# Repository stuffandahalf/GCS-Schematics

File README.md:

# GCS-Schematics
Schematics for my 8-bit computer

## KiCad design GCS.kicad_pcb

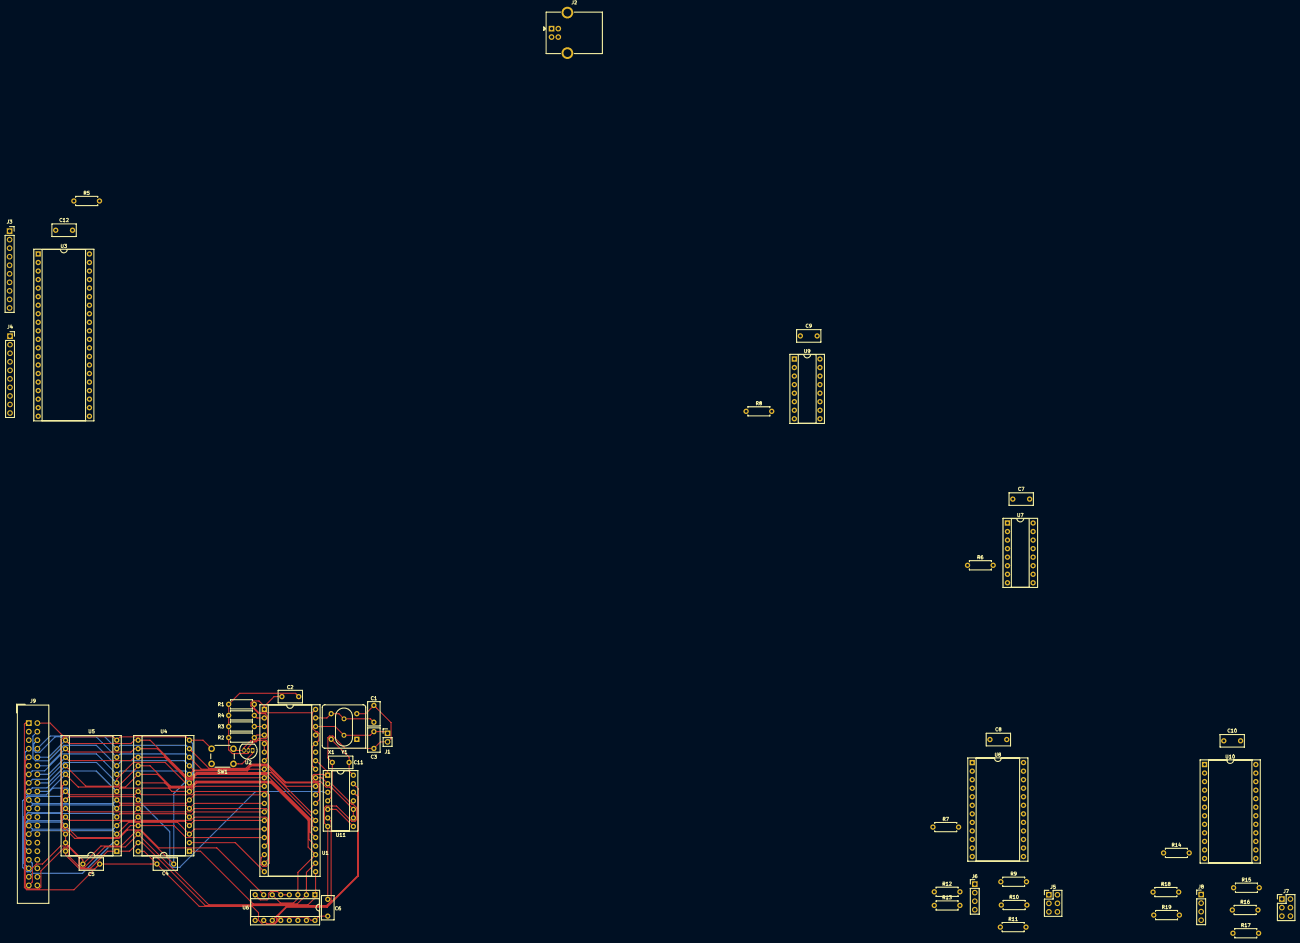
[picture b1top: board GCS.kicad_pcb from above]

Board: 2 copper layers, 54 parts (0 on the bottom side), 91 nets.

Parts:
C1, C3: 15nF; C_Rect_L7.0mm_W3.5mm_P5.00mm
C2, C4, C5, C6, C7, C8, C9, C10, C11, C12: 100nF; C_Rect_L7.0mm_W3.5mm_P5.00mm
J1: PROC_EXTAL_GND; PinHeader_1x02_P2.54mm_Vertical
J2: USB_B; USB_B_OST_USB-B1HSxx_Horizontal
J3: PA_CON; PinSocket_1x10_P2.54mm_Vertical
J4: PB_CON; PinSocket_1x10_P2.54mm_Vertical
J5: ASYNC0_OPT; PinHeader_2x03_P2.54mm_Vertical
J6: ASYNC0_IO; PinHeader_1x04_P2.54mm_Vertical
J7: ASYNC1_OPT; PinHeader_2x03_P2.54mm_Vertical
J8: ASYNC1_IO; PinHeader_1x04_P2.54mm_Vertical
J9: Conn_02x20_Odd_Even; IDC-Header_2x20_P2.54mm_Vertical
R1, R2, R3, R4, R5, R6, R7, R8, R9, R10, R11, R12, R13, R14, R15, R16, R17, R18, R19: 2.7k; R_Axial_DIN0207_L6.3mm_D2.5mm_P7.62mm_Horizontal
SW1: SW_Push; SW_PUSH_6mm
U1: MC6809; DIP-40_W15.24mm_Socket
U2: DS1813; TO-92_Inline
U3: MC68B21; DIP-40_W15.24mm_Socket
U4: HM62256BLP-7; DIP-28_W15.24mm_Socket
U5: 29C256; DIP-28_W15.24mm_Socket
U6, U7, U9: 74LS138; DIP-16_W7.62mm_Socket
U8, U10: MC6850; DIP-24_W15.24mm_Socket
U11: 74HCT00; DIP-14_W7.62mm_Socket
X1: CXO_DIP8; Oscillator_DIP-8
Y1: Crystal; Crystal_HC18-U_Vertical

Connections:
/A0: J9.13, U1.8, U3.36, U4.10, U5.10, U8.11, U10.11
/A1: J9.15, U1.9, U3.35, U4.9, U5.9
/A2: J9.17, U1.10, U4.8, U5.8
/A3: J9.19, U1.11, U4.7, U5.7
/A4: J9.21, U1.12, U4.6, U5.6, U9.1
/A5: J9.23, U1.13, U4.5, U5.5, U9.2
/A6: J9.25, U1.14, U4.4, U5.4, U9.3
/A7: J9.27, U1.15, U4.3, U5.3
/A8: J9.29, U1.16, U4.25, U5.25
/A9: J9.31, U1.17, U4.24, U5.24
/A10: J9.33, U1.18, U4.21, U5.21, U7.1
/A11: J9.35, U1.19, U4.23, U5.23, U7.2
/A12: J9.37, U1.20, U4.2, U5.2, U7.3
/A13: J9.39, U1.21, U4.26, U6.1
/A14: U1.22, U4.1, U6.2
/A15: U1.23, U4.20, U6.3, U6.6
/D0: J9.4, U1.31, U3.33, U4.11, U5.11
/D1: J9.6, U1.30, U3.32, U4.12, U5.12
/D2: J9.8, U1.29, U3.31, U4.13, U5.13
/D3: J9.10, U1.28, U3.30, U4.15, U5.15
/D4: J9.12, U1.27, U3.29, U4.16, U5.16
/D5: J9.14, U1.26, U3.28, U4.17, U5.17
/D6: J9.16, U1.25, U3.27, U4.18, U5.18
/D7: J9.18, U1.24, U3.26, U4.19, U5.19
/E: J9.3, U1.34, U3.25, U8.3, U8.4, U8.14, U10.3, U10.4, U10.14, U11.1, U11.4
/EXTAL: C3.1, J1.1, U1.38, Y1.2
/RX0: R12.2, U8.2
/RX1: R18.2, U10.2
/R~W: J9.5, U1.32, U3.21, U8.13, U10.13, U11.2, U11.9, U11.10
/TX0: R13.2, U8.6
/TX1: R19.2, U10.6
/XTAL: C1.1, U1.39, X1.5, Y1.1
/~ASYNC0_E: U8.9, U9.13
/~ASYNC1_E: U9.12, U10.9
/~BRAM0: U6.11, U11.12
/~BRAM1: U6.10, U11.13
/~CTS0: R10.2, U8.24
/~CTS1: R16.2, U10.24
/~DCD0: R9.2, U8.23
/~DCD1: R15.2, U10.23
/~FIRQ: R2.2, U1.4
/~INT_IO: U7.15, U9.5
/~IO: U6.9, U7.5
/~IRQ: R3.2, U1.3, U3.37, U3.38, U8.7, U10.7
/~NMI: R4.2, U1.2
/~PIA_E: U3.23, U9.14
/~R: J9.7, U4.22, U5.22, U11.3
/~RESET: SW1.2, U1.37, U2.1, U3.34
/~ROM: U5.20, U6.7
/~RTS0: R11.2, U8.5
/~RTS1: R17.2, U10.5
/~R~W: U11.5, U11.8
/~W: J9.9, U4.27, U5.1, U11.6
GND: C1.2, C2.2, C3.2, C4.2, C5.2, C6.2, C7.2, C8.2, C9.2, C10.2, C11.2, C12.2, J1.2, J2.4, J5.2, J5.4, J5.6, J6.1, J7.2, J7.4, J7.6, J8.1, J9.2, SW1.1, U1.1, U2.3, U3.1, U4.14, U5.14, U5.26, U5.27, U6.4, U6.5, U6.8, U7.4, U7.8, U8.1, U9.4, U9.8, U10.1, U11.7, X1.4
unnamed: J3.1, U3.2
unnamed: J3.2, U3.3
unnamed: J3.3, U3.4
unnamed: J3.4, U3.5
unnamed: J3.5, U3.6
unnamed: J3.6, U3.7
unnamed: J3.7, U3.8
unnamed: J3.8, U3.9
unnamed: J3.9, U3.40
unnamed: J3.10, U3.39
unnamed: J4.1, U3.10
unnamed: J4.2, U3.11
unnamed: J4.3, U3.12
unnamed: J4.4, U3.13
unnamed: J4.5, U3.14
unnamed: J4.6, U3.15
unnamed: J4.7, U3.16
unnamed: J4.8, U3.17
unnamed: J4.9, U3.18
unnamed: J4.10, U3.19
unnamed: J5.1, R9.1
unnamed: J5.3, R10.1
unnamed: J5.5, R11.1
unnamed: J6.2, R13.1
unnamed: J6.3, R12.1
unnamed: J7.1, R15.1
unnamed: J7.3, R16.1
unnamed: J7.5, R17.1
unnamed: J8.2, R19.1
unnamed: J8.3, R18.1
unnamed: R1.2, U1.33, U1.36, U1.40
unnamed: R5.1, U3.22, U3.24
unnamed: R6.1, U7.6
unnamed: R7.1, U8.8, U8.10
unnamed: R8.1, U9.6
unnamed: R14.1, U10.8, U10.10
VCC: C2.1, C4.1, C5.1, C6.1, C7.1, C8.1, C9.1, C10.1, C11.1, C12.1, J2.1, J6.4, J8.4, J9.1, R1.1, R2.1, R3.1, R4.1, R5.2, R6.2, R7.2, R8.2, R14.2, U1.7, U2.2, U3.20, U4.28, U5.28, U6.16, U7.16, U8.12, U9.16, U10.12, U11.14, X1.8

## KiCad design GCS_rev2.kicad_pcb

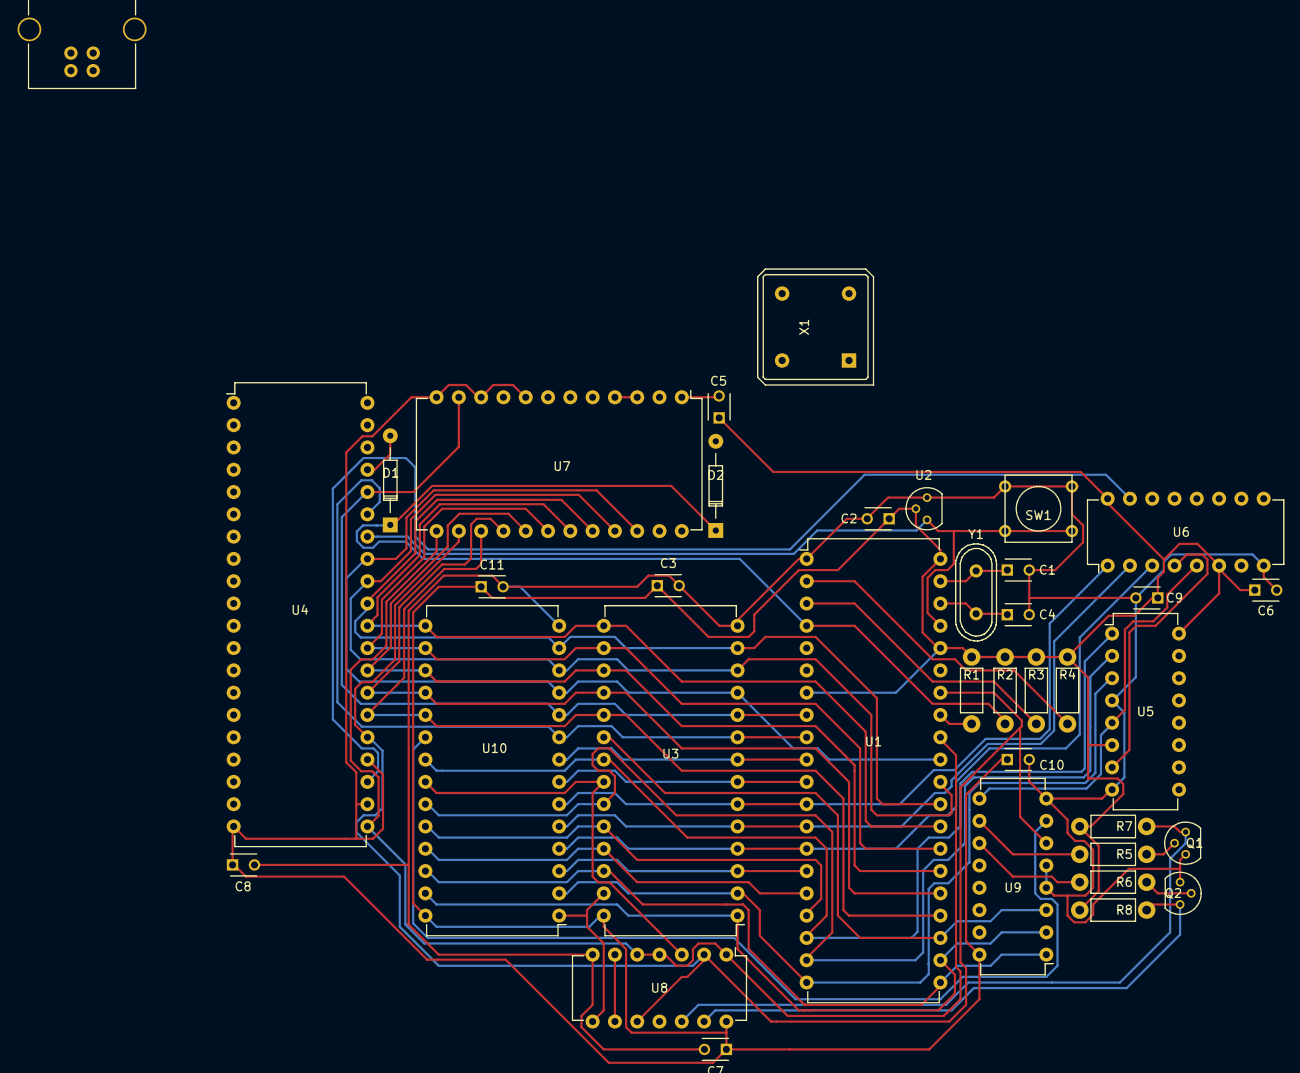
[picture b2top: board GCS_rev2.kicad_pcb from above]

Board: 2 copper layers, 37 parts (0 on the bottom side), 52 nets.

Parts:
C1, C4: 15p; C_Disc_D3_P2.5
C2, C3, C5, C6, C7, C8, C9, C10, C11: .1u; C_Disc_D3_P2.5
D1, D2: D; Diode_DO-35_SOD27_Horizontal_RM10
P1: USB_B
Q1, Q2: 2N3904; TO-92_Molded_Narrow
R1, R2, R3, R4: 4.7k; Resistor_Horizontal_RM7mm
R5, R6: 1k; Resistor_Horizontal_RM7mm
R7, R8: 220; Resistor_Horizontal_RM7mm
SW1: SW_PUSH; SW_PUSH_SMALL
U1: MC6809; DIP-40_W15.24mm
U2: DS1813-5; TO-92_Molded_Narrow
U3: HM62256BLP-7; DIP-28_W15.24mm
U4: 6821; DIP-40_W15.24mm
U5, U6, U9: 74LS138; DIP-16_W7.62mm
U7: MC6850; DIP-24_W15.24mm
U8: 74LS00; DIP-14_W7.62mm
U10: AT29C256-90PI; DIP-28_W15.24mm
X1: CXO_DIP8; OSC_DIP8
Y1: Crystal; Crystal_HC49-U_Vertical

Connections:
/A0: U1.8, U3.10, U4.36, U7.11, U10.10
/A1: U1.9, U3.9, U4.35, U10.9
/A2: U1.10, U3.8, U10.8
/A3: U1.11, U3.7, U10.7
/A4: U1.12, U3.6, U6.1, U10.6
/A5: U1.13, U3.5, U6.2, U10.5
/A6: U1.14, U3.4, U6.3, U10.4
/A7: U1.15, U3.3, U10.3
/A8: U1.16, U3.25, U10.25
/A9: U1.17, U3.24, U10.24
/A10: U1.18, U3.21, U5.1, U10.21
/A11: U1.19, U3.23, U5.2, U10.23
/A12: U1.20, U3.2, U5.3, U10.2
/A13: U1.21, U3.26, U9.1, U10.26
/A14: U1.22, U3.1, U9.2, U10.27
/A15: U1.23, U3.20, U9.3
/D0: U1.31, U3.11, U4.33, U7.22, U10.11
/D1: U1.30, U3.12, U4.32, U7.21, U10.12
/D2: U1.29, U3.13, U4.31, U7.20, U10.13
/D3: U1.28, U3.15, U4.30, U7.19, U10.15
/D4: U1.27, U3.16, U4.29, U7.18, U10.16
/D5: U1.26, U3.17, U4.28, U7.17, U10.17
/D6: U1.25, U3.18, U4.27, U7.16, U10.18
/D7: U1.24, U3.19, U4.26, U7.15, U10.19
/E: U1.34, U4.25, U7.14, U8.2, U8.10, U9.6
/R/~W: U1.32, U4.21, U7.13, U8.1, U8.4, U8.5
/~ASYNC: U6.14, U7.9
/~FIRQ: D1.1, D2.1, R2.2, U1.4
/~IO: U5.5, U6.5, U9.9
/~IRQ: R3.2, U1.3
/~NMI: R4.2, U1.2
/~P7: U5.7, U6.4
/~PIA: U4.23, U6.15
/~R: U3.22, U8.3, U10.22
/~RESET: SW1.1, U1.37, U2.1, U4.34
/~ROM: U9.7, U10.20
/~W: U3.27, U8.8, U10.1
GND: C1.2, C2.2, C3.2, C4.2, C5.2, C6.2, C7.2, C8.2, C9.2, C10.2, C11.2, P1.4, Q1.1, Q2.1, SW1.2, U1.1, U2.3, U3.14, U4.1, U5.4, U5.8, U6.8, U7.1, U8.7, U9.4, U9.5, U9.8, U10.14, X1.4
unnamed: C1.1, U1.39, Y1.1
unnamed: C4.1, U1.38, Y1.2
unnamed: D1.2, U4.37
unnamed: D2.2, U7.7
unnamed: Q1.2, R5.1
unnamed: Q1.3, R7.2, U8.12
unnamed: Q2.2, R6.1
unnamed: Q2.3, R8.2, U8.13
unnamed: R1.2, U1.33
unnamed: R5.2, U9.10
unnamed: R6.2, U9.11
unnamed: U7.3, U7.4, X1.5
unnamed: U8.6, U8.9
VCC: C2.1, C3.1, C5.1, C6.1, C7.1, C8.1, C9.1, C10.1, C11.1, P1.1, R1.1, R2.1, R3.1, R4.1, R7.1, R8.1, U1.7, U1.36, U1.40, U2.2, U3.28, U4.20, U4.22, U4.24, U5.6, U5.16, U6.6, U6.16, U7.8, U7.10, U7.12, U8.14, U9.16, U10.28, X1.8

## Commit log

2019-05-06 Added current schematics
2020-02-29 Added new template on new branch
2020-04-03 Added memory library from kicad v4
2020-04-05 Added redesigned schematics, missing EEPROM
2020-04-05 Added rom
2020-04-06 Added resistors on async io and changed IC footprints to sockets
2020-04-06 Began rerouting PCB
2020-04-06 Combined footprint of crystal and oscillator
2020-04-08 Routed first decoder
2020-04-13 Added header for expandable ram
